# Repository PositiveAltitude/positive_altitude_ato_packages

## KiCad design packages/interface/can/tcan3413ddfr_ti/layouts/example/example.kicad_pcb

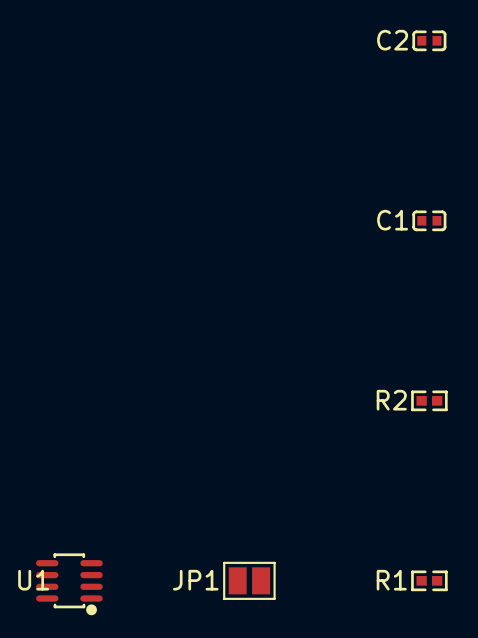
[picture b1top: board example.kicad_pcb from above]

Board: 2 copper layers, 6 parts (0 on the bottom side), 6 nets, no tracks yet.

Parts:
C1, C2: C0402
JP1: SolderJumper-2_P1.3mm_Open_Pad1.0x1.5mm
R1, R2: R0402
U1: SOT-23-8_L2.9-W1.6-P0.65-LS2.8-BR

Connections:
+3.3V: C1.1, C2.1, U1.3, U1.5
A: JP1.1, R2.2
CANH: R2.1, U1.7
CANL: JP1.2, U1.6
GND: C1.2, C2.2, R1.2, U1.2
STB: R1.1, U1.8

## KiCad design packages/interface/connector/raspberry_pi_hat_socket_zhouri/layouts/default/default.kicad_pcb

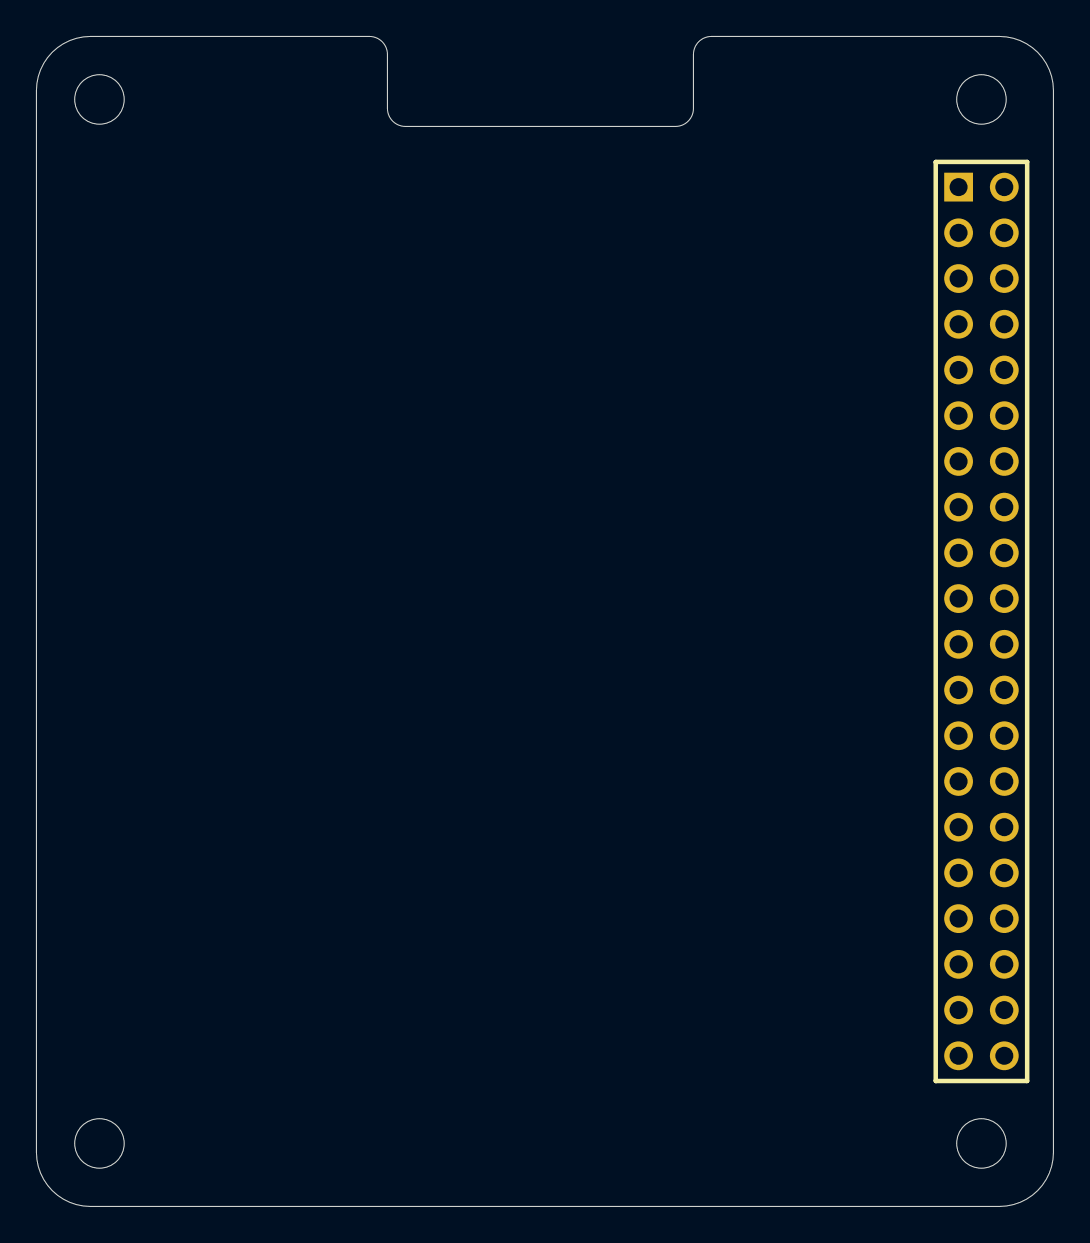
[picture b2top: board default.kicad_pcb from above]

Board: 2 copper layers, 56.5 x 65.0 mm, 5 parts (0 on the bottom side), 3 nets, no tracks yet.

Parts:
H1, H2, H3, H4: Raspberry_Pi_Hat_Mounting_Hole_NPTH
J1: HDR-TH_40P-P2.54-V-F-R2-C20-S2.54

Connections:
hv: J1.1, J1.17
lv: J1.6, J1.9, J1.14, J1.20, J1.25, J1.30, J1.34, J1.39
power_5v0-hv: J1.2, J1.4
